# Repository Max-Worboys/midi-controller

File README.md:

## MIDI Controller
# About
Inspired by my love for music and DJing I have decided to design a midi controller to enhance the software I use.  The controller has 64 buttons and 4 faders and is controlled by an arduino style pro micro with 4 multiplexers.

# PCB

# 3D Model

# Wiring Diagram

# BOM

| Part    | Quantity | Price | Link |
| -------- | ------- | ------- | ------- |
| PCBA | 1 | £55 |
| Pro Micro | 1 | £1 | https://www.aliexpress.com/item/1005007703648261.html?spm=a2g0o.productlist.main.1.56e1cw6gcw6gRu&algo_pvid=c74c5197-ca9e-4478-9e6a-6586243af1f4&algo_exp_id=c74c5197-ca9e-4478-9e6a-6586243af1f4-0&pdp_ext_f=%7B%22order%22%3A%22413%22%2C%22eval%22%3A%221%22%7D&pdp_npi=4%40dis%21GBP%214.47%210.75%21%21%215.87%210.98%21%402103849717495831672693540e099e%2112000041916573235%21sea%21UK%216228885001%21ABX&curPageLogUid=92FfNtIWhhxx&utparam-url=scene%3Asearch%7Cquery_from%3AArduino|
| Multiplexer | 4 | Inclueded in PCB |https://www.mouser.co.uk/ProductDetail/Texas-Instruments/CD74HC4067SM96?qs=JHHQeKcAU3DyfvAOSRLjhQ%3D%3D|
| Switches | 64 | £20 |https://www.aliexpress.com/item/1005008397216226.html?gps-id=pcStoreJustForYou&scm=1007.23125.137358.0&scm_id=1007.23125.137358.0&scm-url=1007.23125.137358.0&pvid=7d8c55b9-f392-417b-bed0-75e97cbf20a1&_t=gps-id:pcStoreJustForYou,scm-url:1007.23125.137358.0,pvid:7d8c55b9-f392-417b-bed0-75e97cbf20a1,tpp_buckets:668%232846%238111%231996&pdp_ext_f=%7B%22order%22%3A%228%22%2C%22eval%22%3A%221%22%2C%22sceneId%22%3A%2213125%22%7D&pdp_npi=4%40dis%21GBP%2113.11%218.16%21%21%2117.22%2110.72%21%402103919917495786328872949e5f4b%2112000044854587062%21rec%21UK%216228885001%21ABXZ&spm=a2g0o.store_pc_home.smartJustForYou_2012872313404.1005008397216226|
| Keycaps | 64 | £16 |https://www.aliexpress.com/item/1005002976015114.html?algo_pvid=3dea6ef6-3e92-4b08-98d0-38158447194a&algo_exp_id=3dea6ef6-3e92-4b08-98d0-38158447194a-0&pdp_ext_f=%7B%22order%22%3A%22175%22%2C%22eval%22%3A%221%22%7D&pdp_npi=4%40dis%21GBP%212.37%211.99%21%21%213.10%212.60%21%40211b61bb17488909333205227ec640%2112000023033844979%21sea%21UK%210%21ABX&curPageLogUid=2NgDAeSoIyT6&utparam-url=scene%3Asearch%7Cquery_from%3A|
| Potentiometer | 4 | £8 |https://www.mouser.co.uk/ProductDetail/Bourns/PTA6043-2015CPB102?qs=QARuOjD9jaE%2Fe2Egjl3azg%3D%3D|
| Protoboard | 1 | £1 |https://www.mouser.co.uk/ProductDetail/Soldered/101734?qs=%252BXxaIXUDbq3DlxvooGHWow%3D%3D|

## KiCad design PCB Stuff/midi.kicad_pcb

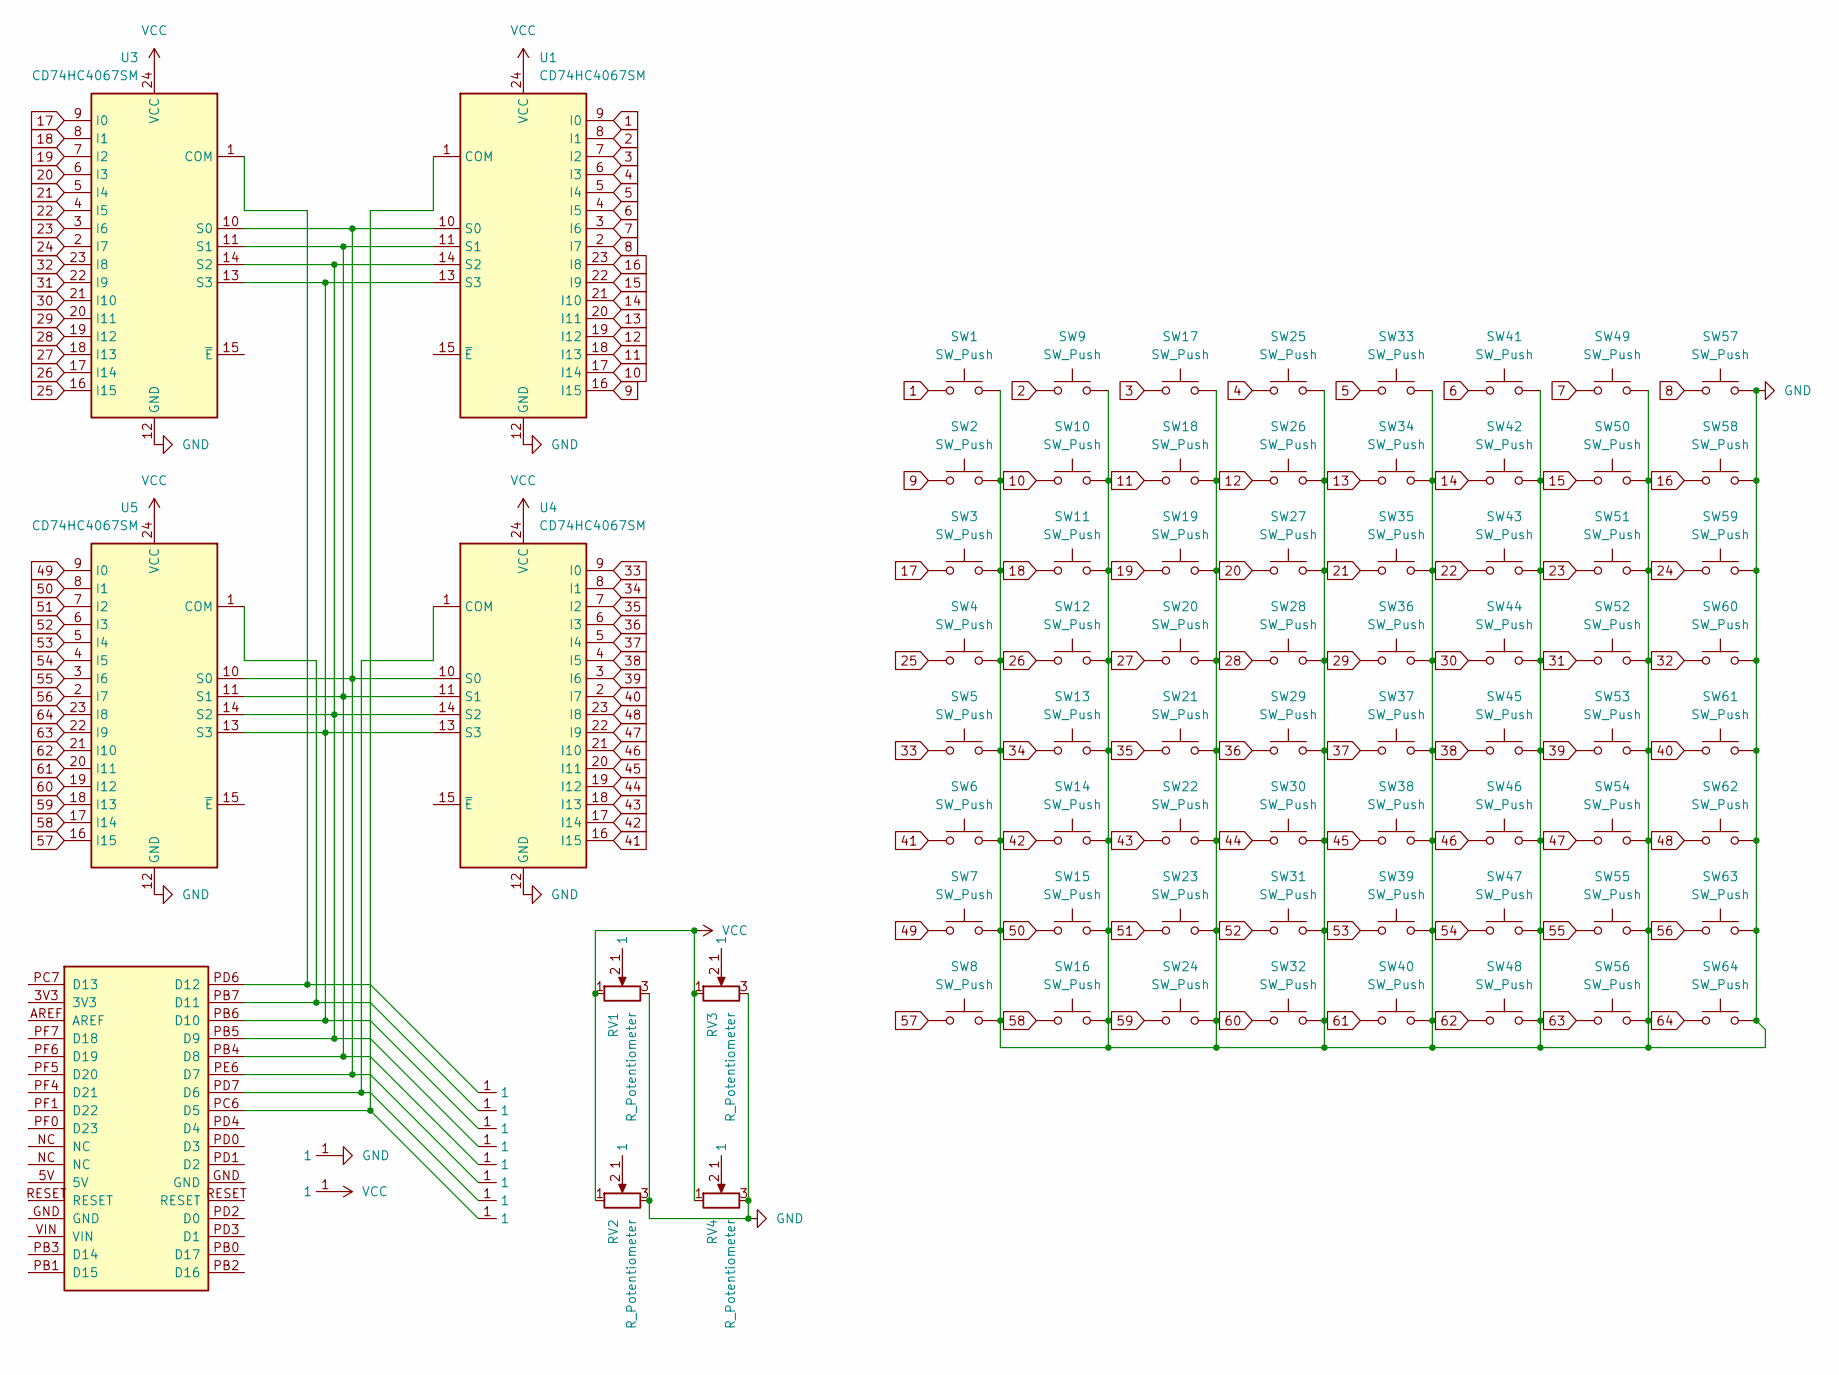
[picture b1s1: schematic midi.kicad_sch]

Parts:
RV1, RV2, RV3, RV4: R_Potentiometer; Potentiometer_Bourns_PTA6043_Single_Slide
SW1, SW2, SW3, SW4, SW5, SW6, SW7, SW8, SW9, SW10, SW11, SW12, SW13, SW14, SW15, SW16, SW17, SW18, SW19, SW20, SW21, SW22, SW23, SW24, SW25, SW26, SW27, SW28, SW29, SW30, SW31, SW32, SW33, SW34, SW35, SW36, SW37, SW38, SW39, SW40, SW41, SW42, SW43, SW44, SW45, SW46, SW47, SW48, SW49, SW50, SW51, SW52, SW53, SW54, SW55, SW56, SW57, SW58, SW59, SW60, SW61, SW62, SW63, SW64: SW_Push; SW_Cherry_MX_1.00u_PCB
U1, U3, U4, U5: CD74HC4067SM; SSOP-24_5.3x8.2mm_P0.65mm
U2: Arduino_Micro
U6, U7, U8, U9, U10, U11, U12, U13, U14, U15, U16, U17, U18, U19: Untitled

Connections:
1: SW1.1, U1.9 (I0)
2: SW9.1, U1.8 (I1)
3: SW17.1, U1.7 (I2)
4: SW25.1, U1.6 (I3)
5: SW33.1, U1.5 (I4)
6: SW41.1, U1.4 (I5)
7: SW49.1, U1.3 (I6)
8: SW57.1, U1.2 (I7)
9: SW2.1, U1.16 (I15)
10: SW10.1, U1.17 (I14)
11: SW18.1, U1.18 (I13)
12: SW26.1, U1.19 (I12)
13: SW34.1, U1.20 (I11)
14: SW42.1, U1.21 (I10)
15: SW50.1, U1.22 (I9)
16: SW58.1, U1.23 (I8)
17: SW3.1, U3.9 (I0)
18: SW11.1, U3.8 (I1)
19: SW19.1, U3.7 (I2)
20: SW27.1, U3.6 (I3)
21: SW35.1, U3.5 (I4)
22: SW43.1, U3.4 (I5)
23: SW51.1, U3.3 (I6)
24: SW59.1, U3.2 (I7)
25: SW4.1, U3.16 (I15)
26: SW12.1, U3.17 (I14)
27: SW20.1, U3.18 (I13)
28: SW28.1, U3.19 (I12)
29: SW36.1, U3.20 (I11)
30: SW44.1, U3.21 (I10)
31: SW52.1, U3.22 (I9)
32: SW60.1, U3.23 (I8)
33: SW5.1, U4.9 (I0)
34: SW13.1, U4.8 (I1)
35: SW21.1, U4.7 (I2)
36: SW29.1, U4.6 (I3)
37: SW37.1, U4.5 (I4)
38: SW45.1, U4.4 (I5)
39: SW53.1, U4.3 (I6)
40: SW61.1, U4.2 (I7)
41: SW6.1, U4.16 (I15)
42: SW14.1, U4.17 (I14)
43: SW22.1, U4.18 (I13)
44: SW30.1, U4.19 (I12)
45: SW38.1, U4.20 (I11)
46: SW46.1, U4.21 (I10)
47: SW54.1, U4.22 (I9)
48: SW62.1, U4.23 (I8)
49: SW7.1, U5.9 (I0)
50: SW15.1, U5.8 (I1)
51: SW23.1, U5.7 (I2)
52: SW31.1, U5.6 (I3)
53: SW39.1, U5.5 (I4)
54: SW47.1, U5.4 (I5)
55: SW55.1, U5.3 (I6)
56: SW63.1, U5.2 (I7)
57: SW8.1, U5.16 (I15)
58: SW16.1, U5.17 (I14)
59: SW24.1, U5.18 (I13)
60: SW32.1, U5.19 (I12)
61: SW40.1, U5.20 (I11)
62: SW48.1, U5.21 (I10)
63: SW56.1, U5.22 (I9)
64: SW64.1, U5.23 (I8)
GND: RV1.3, RV2.3, RV3.3, RV4.3, SW1.2, SW2.2, SW3.2, SW4.2, SW5.2, SW6.2, SW7.2, SW8.2, SW9.2, SW10.2, SW11.2, SW12.2, SW13.2, SW14.2, SW15.2, SW16.2, SW17.2, SW18.2, SW19.2, SW20.2, SW21.2, SW22.2, SW23.2, SW24.2, SW25.2, SW26.2, SW27.2, SW28.2, SW29.2, SW30.2, SW31.2, SW32.2, SW33.2, SW34.2, SW35.2, SW36.2, SW37.2, SW38.2, SW39.2, SW40.2, SW41.2, SW42.2, SW43.2, SW44.2, SW45.2, SW46.2, SW47.2, SW48.2, SW49.2, SW50.2, SW51.2, SW52.2, SW53.2, SW54.2, SW55.2, SW56.2, SW57.2, SW58.2, SW59.2, SW60.2, SW61.2, SW62.2, SW63.2, SW64.2, U1.12 (GND), U3.12 (GND), U4.12 (GND), U5.12 (GND), U18.1
unnamed: RV1.2, U9.1
unnamed: RV2.2, U8.1
unnamed: RV3.2, U6.1
unnamed: RV4.2, U7.1
unnamed: U1.1 (COM), U2.PC6 (D5), U13.1
unnamed: U1.10 (S0), U2.PE6 (D7), U3.10 (S0), U4.10 (S0), U5.10 (S0), U11.1
unnamed: U1.11 (S1), U2.PB4 (D8), U3.11 (S1), U4.11 (S1), U5.11 (S1), U10.1
unnamed: U1.14 (S2), U2.PB5 (D9), U3.14 (S2), U4.14 (S2), U5.14 (S2), U17.1
unnamed: U1.13 (S3), U2.PB6 (D10), U3.13 (S3), U4.13 (S3), U5.13 (S3), U16.1
unnamed: U2.PD7 (D6), U4.1 (COM), U12.1
unnamed: U2.PB7 (D11), U5.1 (COM), U15.1
unnamed: U2.PD6 (D12), U3.1 (COM), U14.1
VCC: RV1.1, RV2.1, RV3.1, RV4.1, U1.24 (VCC), U3.24 (VCC), U4.24 (VCC), U5.24 (VCC), U19.1

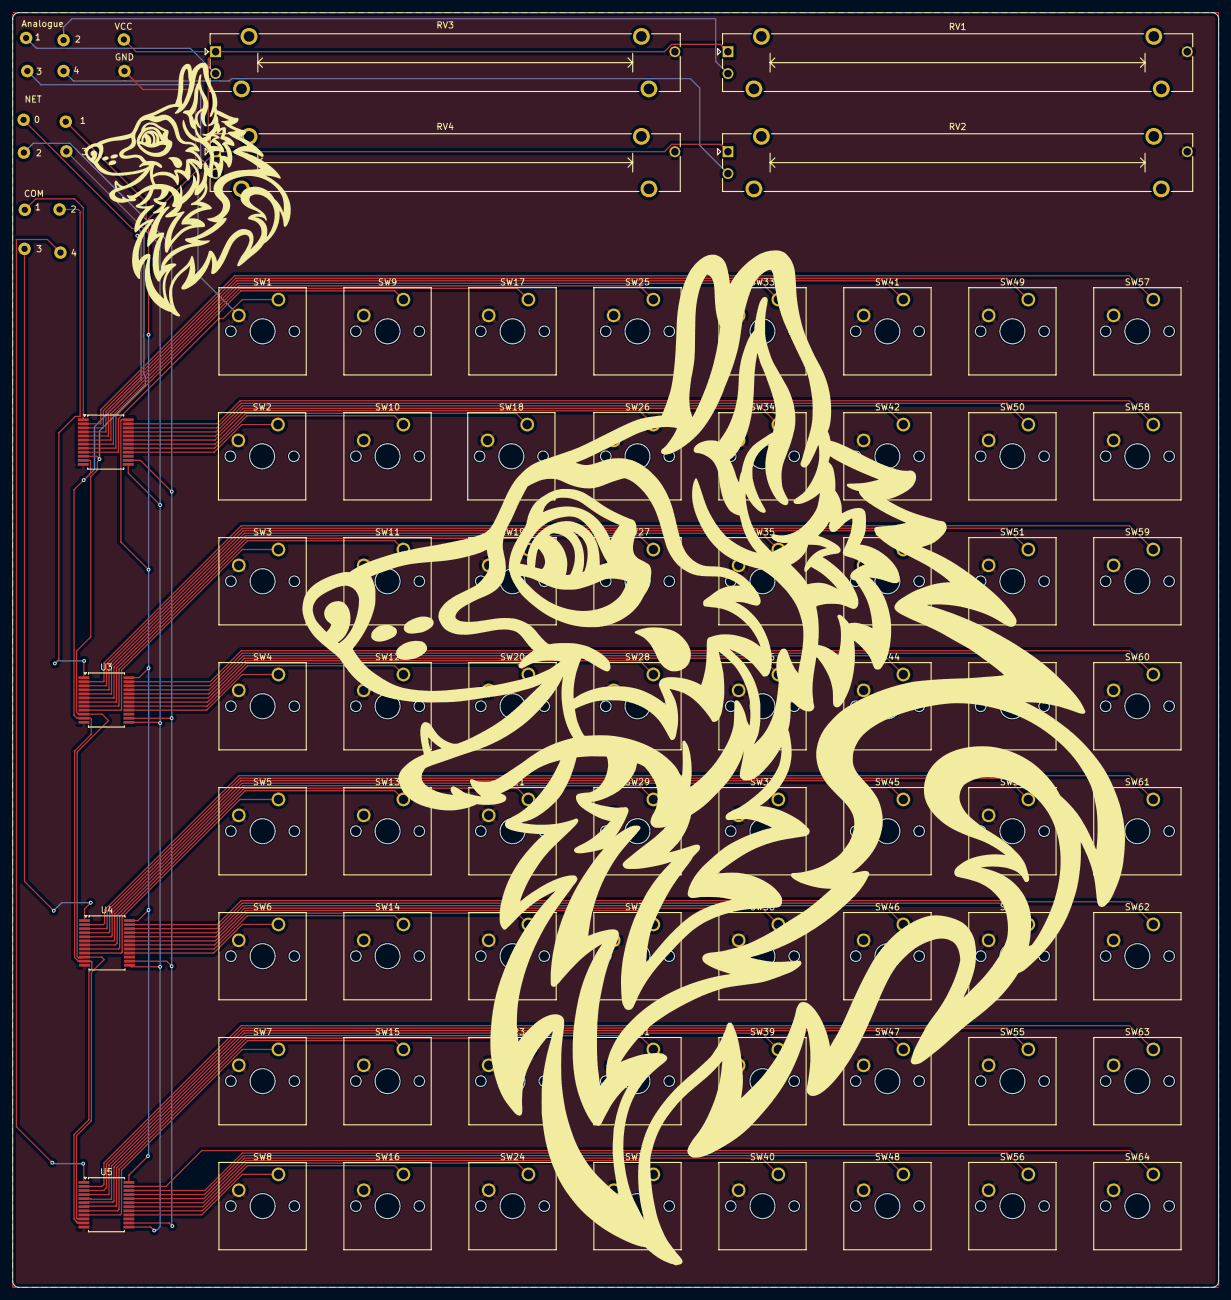
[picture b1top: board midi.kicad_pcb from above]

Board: 2 copper layers, 193.0 x 204.0 mm, 86 parts (0 on the bottom side), 78 nets.

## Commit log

2025-06-03 Rename image.png to assets/more_accurate_pricing.png
2025-06-03 Rename more_accurate_pricing.png to More_Accurate_Pricing.png
2025-06-05 Rename Midi Bottom.stl to Midi Bottom.stl
2025-06-05 Rename Midi Top.stl to Midi Top.stl
2025-08-01 Create Production
2025-08-01 Rename MidiCodeNew.ino to Code/MidiCodeNew.ino
